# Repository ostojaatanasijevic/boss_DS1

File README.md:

# TPI pedals - BSDS1

## Schematic

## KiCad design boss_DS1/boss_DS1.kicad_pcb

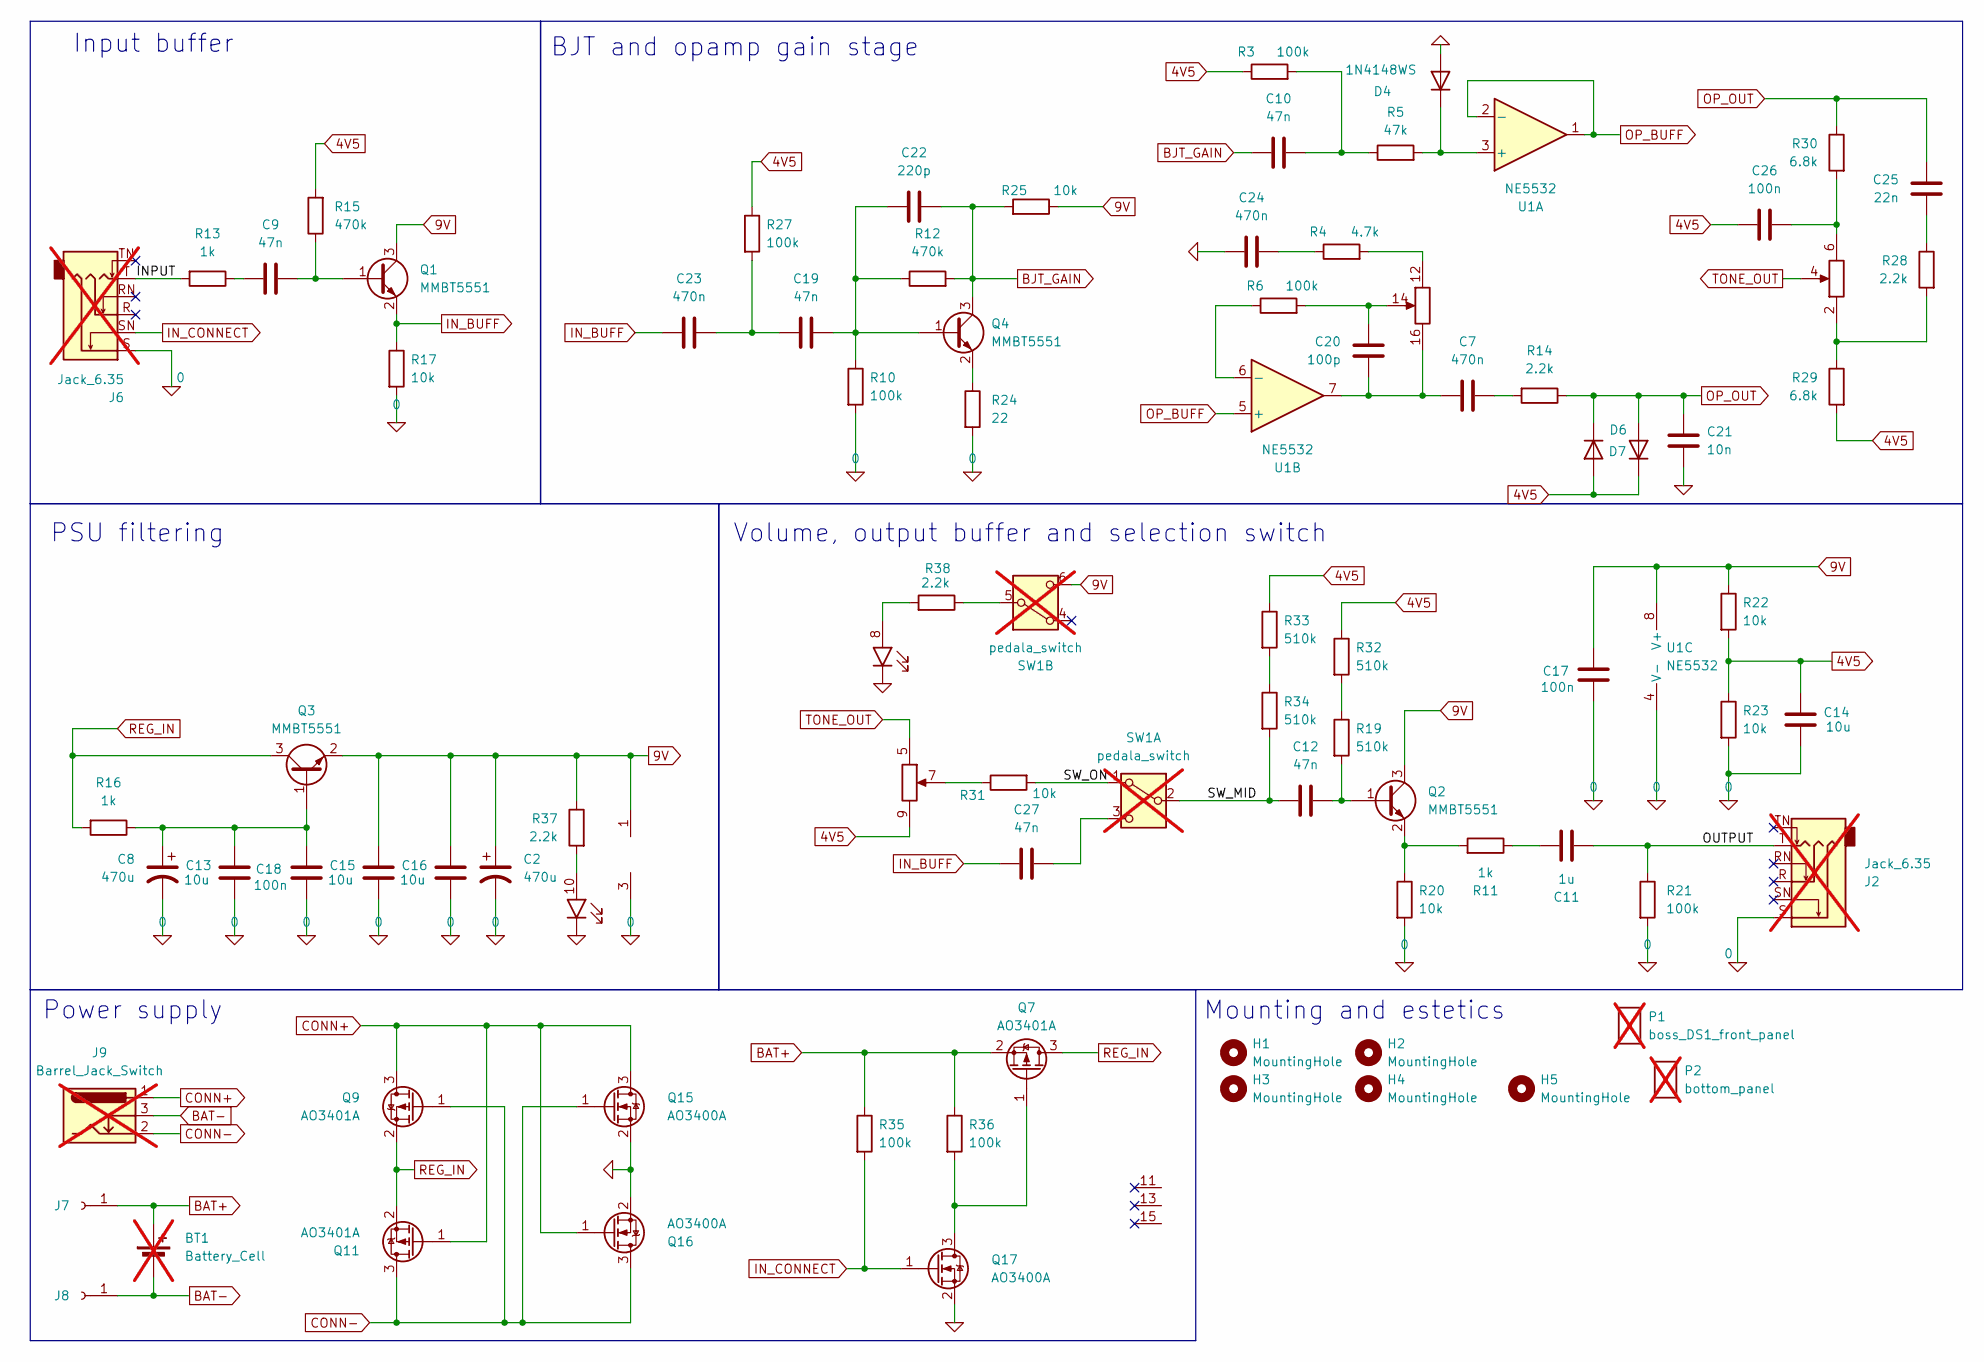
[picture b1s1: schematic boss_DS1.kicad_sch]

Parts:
BT1: Battery_Cell; BatteryHolder_Eagle_12BH611-GR; not fitted
C2, C8: 470u; CP_Radial_D8.0mm_P3.50mm
C7, C23, C24: 470n; C_0603_1608Metric_Pad1.08x0.95mm_HandSolder; LCSC C1623
C9, C10, C12, C19, C27: 47n; C_0603_1608Metric_Pad1.08x0.95mm_HandSolder; LCSC C1622
C11: 1u; C_0603_1608Metric_Pad1.08x0.95mm_HandSolder; LCSC C15849
C13, C14, C15, C16: 10u; C_0603_1608Metric_Pad1.08x0.95mm_HandSolder; LCSC C96446
C17, C18, C26: 100n; C_0603_1608Metric_Pad1.08x0.95mm_HandSolder; LCSC C14663
C20: 100p; C_0603_1608Metric_Pad1.08x0.95mm_HandSolder; LCSC C14858
C21: 10n; C_0603_1608Metric_Pad1.08x0.95mm_HandSolder; LCSC C57112
C22: 220p; C_0603_1608Metric_Pad1.08x0.95mm_HandSolder; LCSC C1603
C25: 22n; C_0603_1608Metric_Pad1.08x0.95mm_HandSolder; LCSC C21122
D4, D6, D7: 1N4148WS; D_SOD-323; LCSC C2128
H1, H2, H3, H4, H5: MountingHole; M3_hole_with_spacer
J1: top_panel_connector; IDC-Header_2x08_P2.54mm_Vertical
J2, J6: Jack_6.35; Jack_6.35mm; not fitted
J7, J8: Conn_01x01_Socket; TestPoint_THTPad_D2.5mm_Drill1.2mm
J9: Barrel_Jack_Switch; BarrelJack; not fitted
P1: boss_DS1_front_panel; boss_DS1_front_plate; not fitted
P2: bottom_panel; bottom_plate; not fitted
Q1, Q2, Q3, Q4: MMBT5551; SOT-23; LCSC C2145
Q7, Q9, Q11: AO3401A; SOT-23; LCSC C15127
Q15, Q16, Q17: AO3400A; SOT-23; LCSC C20917
R3, R6, R10, R21, R27, R35, R36: 100k; R_0603_1608Metric_Pad0.98x0.95mm_HandSolder; LCSC C25803
R4: 4.7k; R_0603_1608Metric_Pad0.98x0.95mm_HandSolder; LCSC C23162
R5: 47k; R_0603_1608Metric_Pad0.98x0.95mm_HandSolder; LCSC C25819
R11, R13, R16: 1k; R_0603_1608Metric_Pad0.98x0.95mm_HandSolder; LCSC C21190
R12, R15: 470k; R_0603_1608Metric_Pad0.98x0.95mm_HandSolder; LCSC C23178
R14, R28, R37, R38: 2.2k; R_0603_1608Metric_Pad0.98x0.95mm_HandSolder; LCSC C4190
R17, R20, R22, R23, R25, R31: 10k; R_0603_1608Metric_Pad0.98x0.95mm_HandSolder; LCSC C25804
R19, R32, R33, R34: 510k; R_0603_1608Metric_Pad0.98x0.95mm_HandSolder; LCSC C23192
R24: 22; R_0603_1608Metric_Pad0.98x0.95mm_HandSolder; LCSC C23345
R29, R30: 6.8k; R_0603_1608Metric_Pad0.98x0.95mm_HandSolder; LCSC C23212
SW1: pedala_switch; foot_switch_tht_no_pad; not fitted
U1: NE5532; SOIC-8_3.9x4.9mm_P1.27mm; LCSC C7426

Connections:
0: C2.2, C8.2, C13.2, C14.2, C15.2, C16.2, C17.1, C18.1, C21.1, C24.1, D4.2 (A), J1.3 (GND), J2.S, J6.S, Q15.2 (S), Q16.2 (S), Q17.2 (S), R10.2, R17.2, R20.2, R21.2, R23.2, R24.2, U1.4 (V-)
4V5: C14.1, C26.2, D6.2 (A), D7.1 (K), J1.9, R3.1, R15.2, R22.2, R23.1, R27.1, R29.2, R32.1, R33.1
9V: C2.1, C15.1, C16.1, C17.2, J1.1 (VCC), Q1.3 (C), Q2.3 (C), Q3.2 (E), R22.1, R25.1, R37.1, SW1.6 (C), U1.8 (V+)
/INPUT: J6.T, R13.2
/OUTPUT: C11.2, J2.T, R21.1
/SW_MID: C12.1, R34.2, SW1.2 (B)
/SW_ON: R31.2, SW1.1 (A)
BAT+: BT1.1 (+), J7.1, Q7.2 (S), R35.1, R36.1
BAT-: BT1.2 (-), J8.1, J9.3
BJT_GAIN: C10.1, C22.2, Q4.3 (C), R12.2, R25.2
CONN+: J9.1, Q9.3 (D), Q11.1 (G), Q15.3 (D), Q16.1 (G)
CONN-: J9.2, Q9.1 (G), Q11.3 (D), Q15.1 (G), Q16.3 (D)
IN_BUFF: C23.1, C27.1, Q1.2 (E), R17.1
IN_CONNECT: J6.SN, Q17.1 (G), R35.2
unnamed: C7.2, R14.2
unnamed: C9.1, R13.1
unnamed: C10.2, R3.2, R5.1
unnamed: C11.1, R11.1
unnamed: C19.1, C23.2, R27.2
unnamed: C24.2, R4.1
unnamed: C25.1, R28.1
unnamed: D4.1 (K), R5.2, U1.3 (+)
unnamed: J1.2, R28.2, R29.1
unnamed: C26.1, J1.6, R30.2
unnamed: J1.7, R31.1
unnamed: J1.12, R4.2
unnamed: C20.2, J1.14, R6.2
unnamed: C7.1, C20.1, J1.16, U1.7
unnamed: J1.8, R38.2
unnamed: J1.10, R37.2
unnamed: C9.2, Q1.1 (B), R15.1
unnamed: C12.2, Q2.1 (B), R19.2
unnamed: Q2.2 (E), R11.2, R20.1
unnamed: C8.1, C13.1, C18.2, Q3.1 (B), R16.1
unnamed: C19.2, C22.1, Q4.1 (B), R10.1, R12.1
unnamed: Q4.2 (E), R24.1
unnamed: Q7.1 (G), Q17.3 (D), R36.2
unnamed: R19.1, R32.2
unnamed: R33.2, R34.1
unnamed: C27.2, SW1.3 (C)
unnamed: R38.1, SW1.5 (B)
unnamed: R6.1, U1.6 (-)
OP_BUFF: U1.1, U1.2 (-), U1.5 (+)
OP_OUT: C21.2, C25.2, D6.1 (K), D7.2 (A), R14.1, R30.1
REG_IN: Q3.3 (C), Q7.3 (D), Q9.2 (S), Q11.2 (S), R16.2
TONE_OUT: J1.4, J1.5

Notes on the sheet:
Input buffer
Mounting and estetics
PSU filtering
BJT and opamp gain stage
Volume, output buffer and selection switch
Power supply

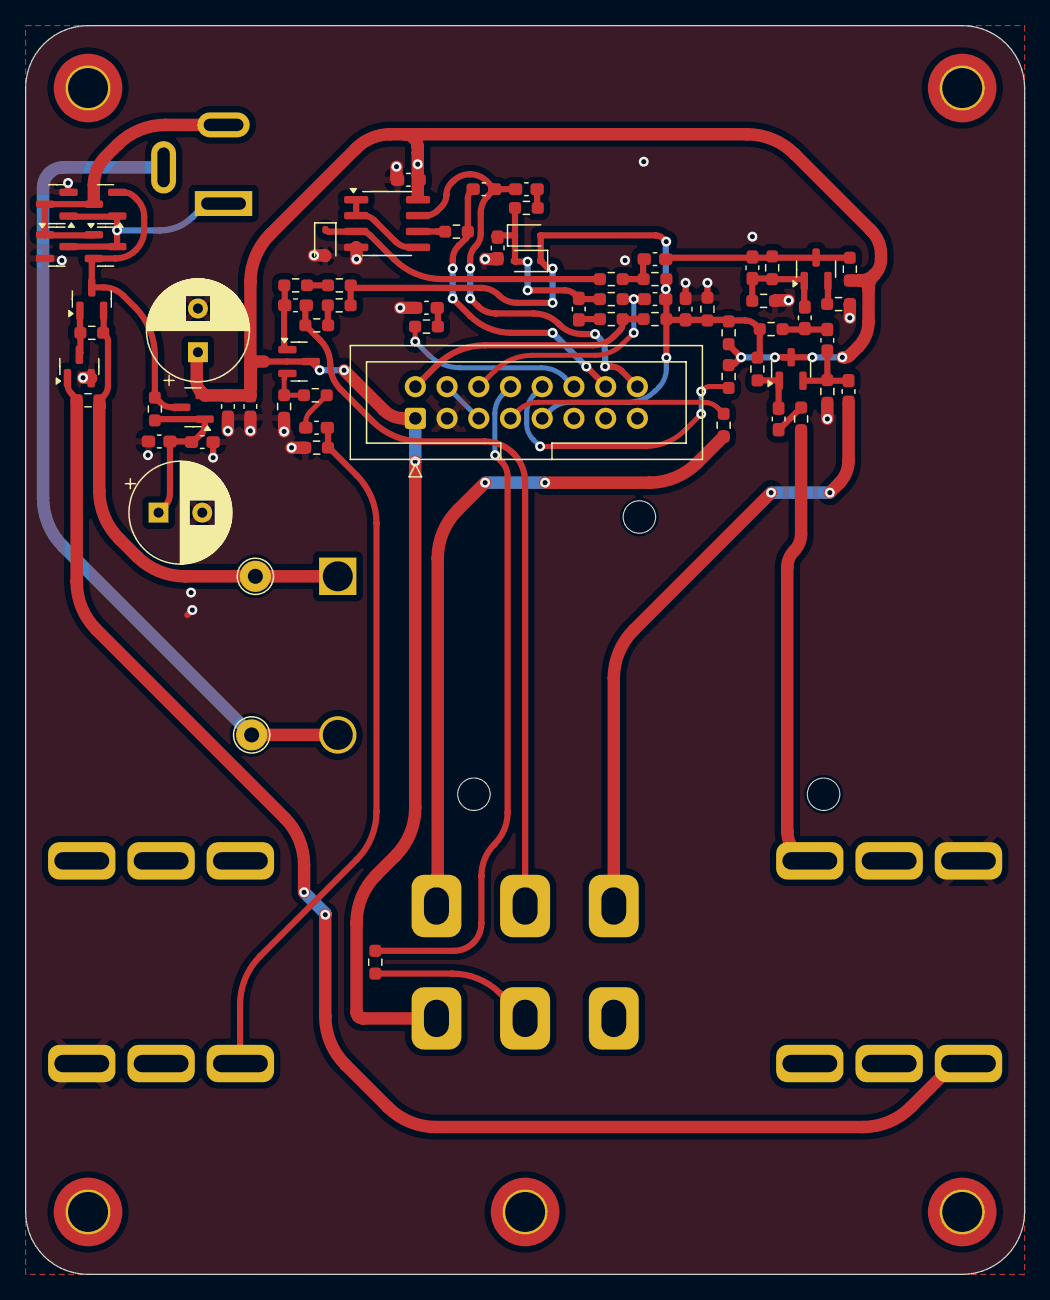
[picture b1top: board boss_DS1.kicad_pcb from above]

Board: 2 copper layers, 80.0 x 100.0 mm, 84 parts (0 on the bottom side), 46 nets.

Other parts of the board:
D8: floating_green_led
D9: floating_red_led

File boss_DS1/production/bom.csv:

Designator,Footprint,Quantity,Value,LCSC Part #
"C10, C12, C19, C27, C9",0603,5,47n,C1622
C11,0603,1,1u,C15849
"C13, C14, C15, C16",0603,4,10u,C96446
"C17, C18, C26",0603,3,100n,C14663
C20,0603,1,100p,C14858
C21,0603,1,10n,C57112
C22,0603,1,220p,C1603
"C23, C24, C7",0603,3,470n,C1623
C25,0603,1,22n,C21122
"D4, D6, D7",D_SOD-323,3,1N4148WS,C2128
"Q1, Q2, Q3, Q4",SOT-23,4,MMBT5551,C2145
"Q11, Q7, Q9",SOT-23,3,AO3401A,C15127
"Q15, Q16, Q17",SOT-23,3,AO3400A,C20917
"R10, R21, R27, R3, R35, R36, R6",0603,7,100k,C25803
"R11, R13, R16",0603,3,1k,C21190
"R12, R15",0603,2,470k,C23178
"R14, R28, R37, R38",0603,4,2.2k,C4190
"R17, R20, R22, R23, R25, R31",0603,6,10k,C25804
"R19, R32, R33, R34",0603,4,510k,C23192
R24,0603,1,22,C23345
"R29, R30",0603,2,6.8k,C23212
R4,0603,1,4.7k,C23162
R5,0603,1,47k,C25819
U1,SOIC-8_3.9x4.9mm_P1.27mm,1,NE5532,C7426

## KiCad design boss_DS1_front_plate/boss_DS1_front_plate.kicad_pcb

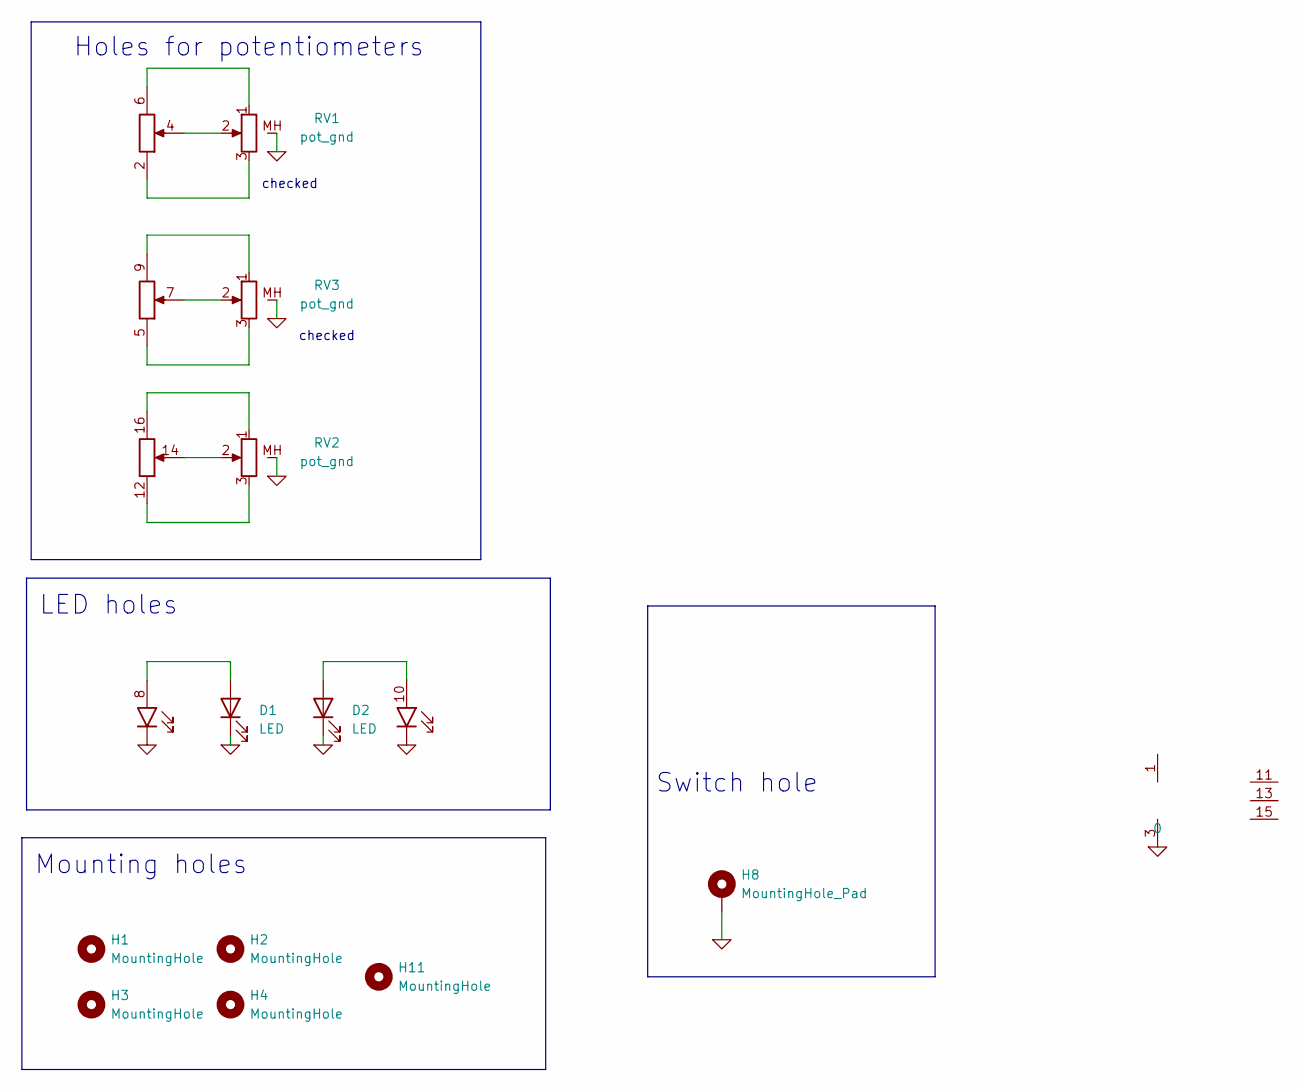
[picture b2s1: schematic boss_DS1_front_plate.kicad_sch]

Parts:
D1: LED; red_led
D2: LED; green_led
H1, H2, H3, H4, H11: MountingHole; MountingHole_3.2mm_M3_DIN965_Pad_TopBottom
H8: MountingHole_Pad; plated_switch_hole
J1: top_panel_connector; IDC-Header_2x08_P2.54mm_Vertical
RV1, RV2, RV3: pot_gnd; top_plate_pot

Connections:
0: D1.1 (K), D2.1 (K), H8.1, J1.3 (GND), RV1.MH (2), RV2.MH (2), RV3.MH (2)
unnamed: D1.2 (A), J1.8
unnamed: D2.2 (A), J1.10
unnamed: J1.2, RV1.3
unnamed: J1.4, RV1.2
unnamed: J1.6, RV1.1
unnamed: J1.5, RV3.3
unnamed: J1.7, RV3.2
unnamed: J1.9, RV3.1
unnamed: J1.12, RV2.3
unnamed: J1.14, RV2.2
unnamed: J1.16, RV2.1

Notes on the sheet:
Holes for potentiometers
checked
LED holes
Mounting holes
Switch hole

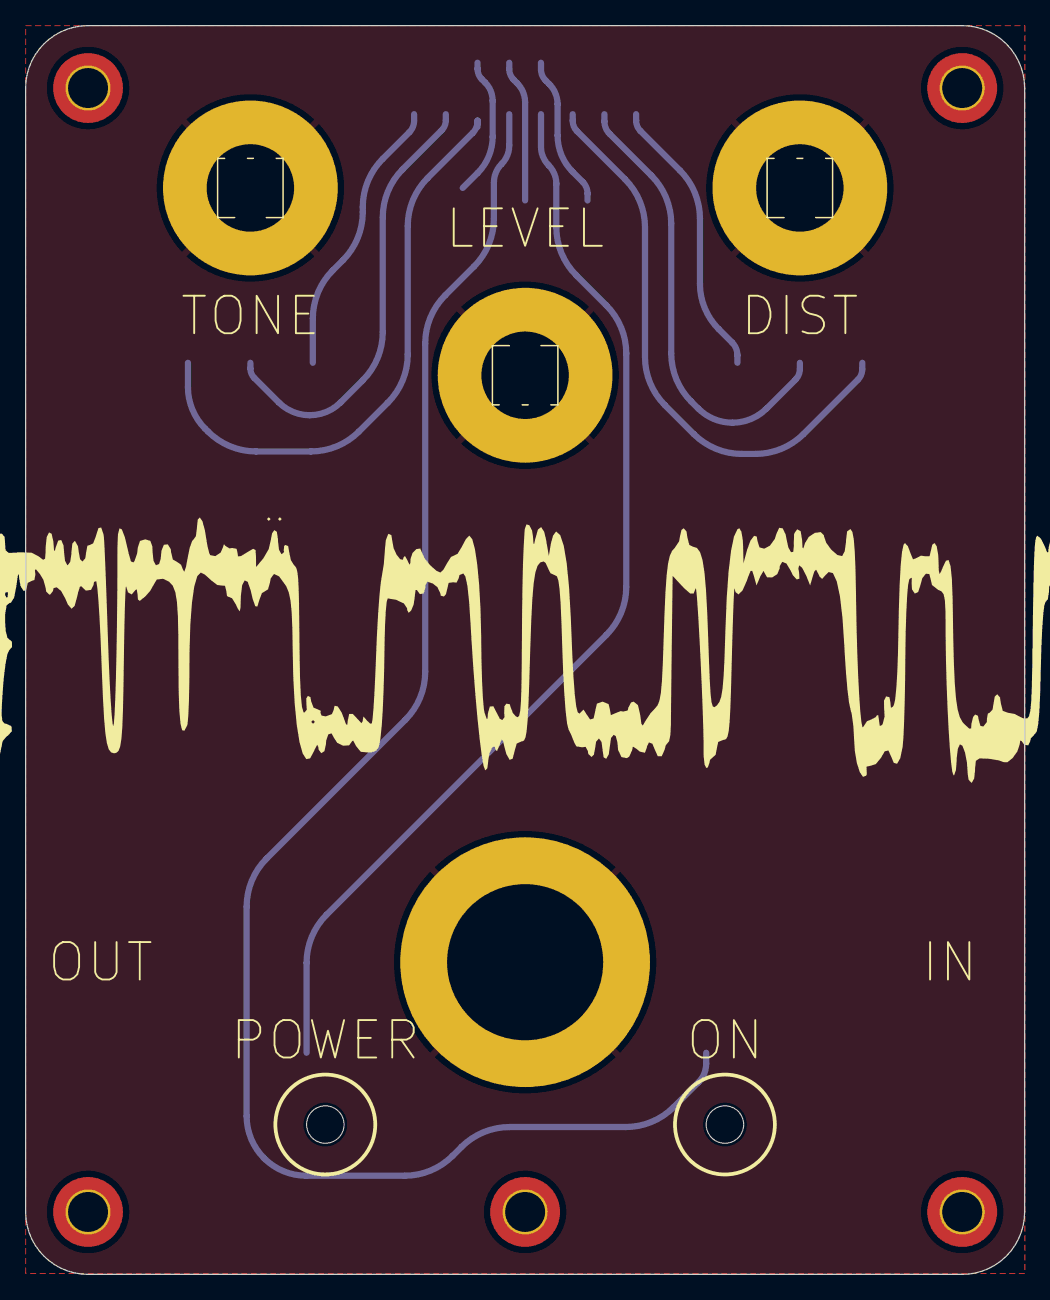
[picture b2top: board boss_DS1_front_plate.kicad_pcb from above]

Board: 2 copper layers, 80.0 x 100.0 mm, 12 parts (1 on the bottom side), 12 nets.

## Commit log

2025-04-02 Init.
2025-04-02 fix.
2025-04-04 rutiranje v1.
2025-04-04 rutiranje v2.
2025-04-04 Rutiranje v3
2025-04-04 verzija v4
2025-04-05 All errors fixed
2025-04-06 Updated front plate
2025-05-09 newnewe
2025-05-09 New phone who dis.
2025-05-13 Added plate proj.
2025-05-13 gene.
2025-05-13 Updated front.
2025-05-21 Updated libs.
2025-05-22 Potentiometers checked.
2025-05-22 Pots again, done.
2025-05-22 Top plate routiran, valja proveriti pot-ove opet.
2025-05-22 Front plate update, diodes rotated.
2025-05-22 Added pot value label.
2025-05-22 Top plate rounded.
2025-05-22 Rutiranje gotovo
2025-05-22 updated conn
2025-05-22 3d models update.
2025-05-22 fsdflaksj
2025-05-22 dsaf.
2025-05-22 Updated all.
2025-05-22 dfsa.
2025-05-22 Rounded traces.
2025-05-24 Ready for production.
2025-05-24 Updated README.
2025-05-24 Updated.
2025-05-24 saving v1.
2025-05-24 Readme.
